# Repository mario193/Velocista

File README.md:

# Velocista
Un robot muy rápido

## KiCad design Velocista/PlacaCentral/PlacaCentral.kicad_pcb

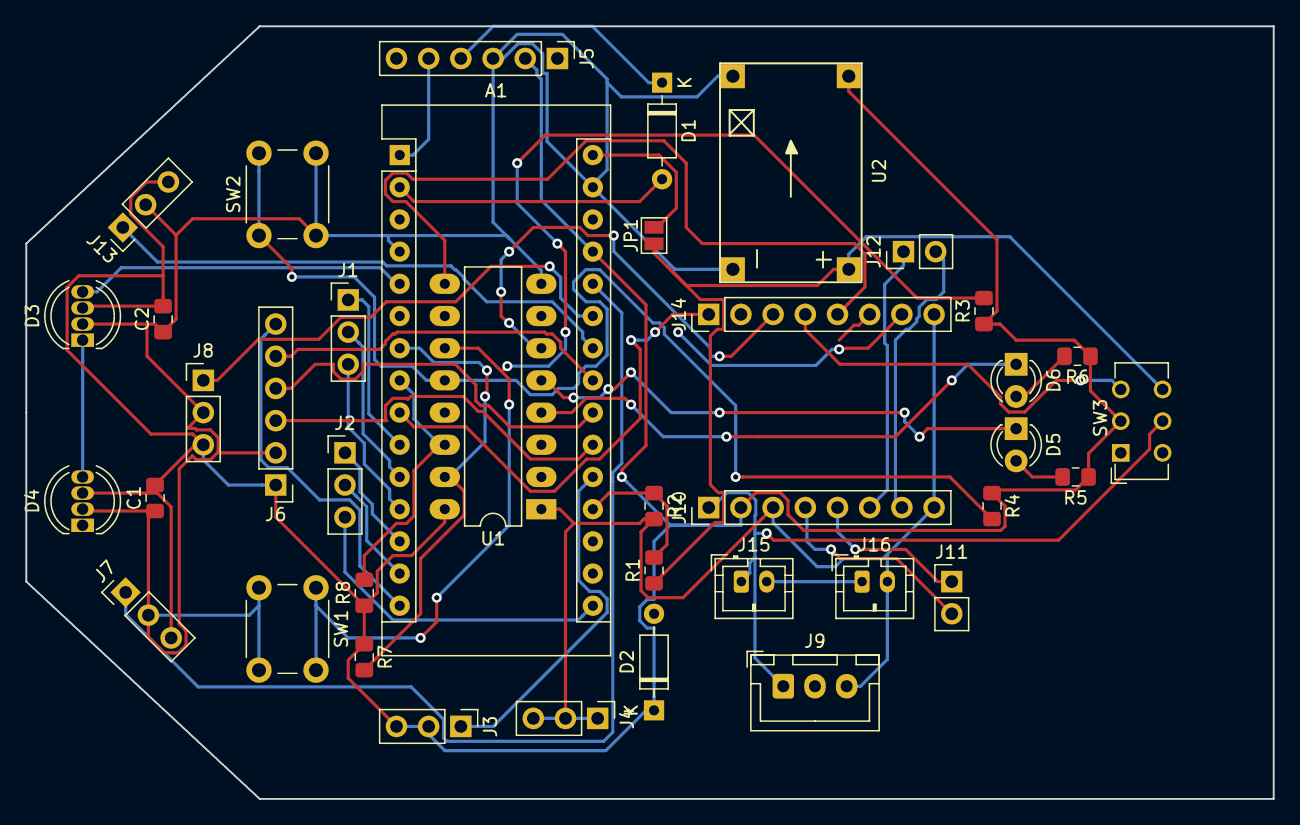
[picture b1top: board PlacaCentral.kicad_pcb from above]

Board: 2 copper layers, 98.4 x 61.0 mm, 39 parts (0 on the bottom side), 45 nets.

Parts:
A1: Arduino_Nano_v3.x; Arduino_Nano
C1, C2: 100nF; C_0805_2012Metric_Pad1.15x1.40mm_HandSolder
D1, D2: 1N4148; D_DO-35_SOD27_P7.62mm_Horizontal
D3: NEO1; LED_D5.0mm-4_RGB
D4: NEO2; LED_D5.0mm-4_RGB
D5: ROJO; LED_D3.0mm
D6: VERDE; LED_D3.0mm
J1: AUX1; PinHeader_1x03_P2.54mm_Vertical
J2: AUX2; PinHeader_1x03_P2.54mm_Vertical
J3: AUX3; PinHeader_1x03_P2.54mm_Vertical
J4: AUX4; PinHeader_1x03_P2.54mm_Vertical
J5: HC-05; PinHeader_1x06_P2.54mm_Vertical
J6: Sensores_linea; PinHeader_1x06_P2.54mm_Vertical
J7: DIST_IZQ; PinHeader_1x03_P2.54mm_Vertical
J8: DIST_FRONT; PinHeader_1x03_P2.54mm_Vertical
J9: LIPO_2S; JST_XH_B03B-XH-A_1x03_P2.50mm_Vertical
J10: TB6612FNG_A; PinHeader_1x08_P2.54mm_Vertical
J11: MOT_IZQ; PinHeader_1x02_P2.54mm_Vertical
J12: MOT_DER; PinHeader_1x02_P2.54mm_Vertical
J13: DIST_DCHA; PinHeader_1x03_P2.54mm_Vertical
J14: TB6612FNG_B; PinHeader_1x08_P2.54mm_Vertical
J15: LIPO_1S_A; JST_PH_B2B-PH-K_1x02_P2.00mm_Vertical
J16: LIPO_1S_B; JST_PH_B2B-PH-K_1x02_P2.00mm_Vertical
JP1: Jumper_NO_Small; SolderJumper-2_P1.3mm_Open_Pad1.0x1.5mm
R1: 82K; R_0805_2012Metric_Pad1.15x1.40mm_HandSolder
R2: 120K; R_0805_2012Metric_Pad1.15x1.40mm_HandSolder
R3, R4: 10K; R_0805_2012Metric_Pad1.15x1.40mm_HandSolder
R5, R6: 220; R_0805_2012Metric_Pad1.15x1.40mm_HandSolder
R7, R8: 1K; R_0805_2012Metric_Pad1.15x1.40mm_HandSolder
SW1: B1; SW_PUSH_6mm
SW2: B2; SW_PUSH_6mm
SW3: SW_DPDT_x2; SW_CuK_JS202011CQN_DPDT_Straight
U1: PCF8574; DIP-16_W7.62mm_LongPads
U2: DC-DC_BuckModule; DC-DC-MP2307

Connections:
12C_SCL: A1.8, R8.2, U1.14
12C_SDA: A1.7, R7.2, U1.15
+5V: A1.27, C1.2, C2.2, D2.1, D3.3, D4.3, J3.2, J3.3, J5.2, J6.1, J7.3, J8.3, J10.2, J13.3, R3.1, R4.1, R5.1, R6.1, R7.1, R8.1, SW3.2, U1.16, U2.3
A1: A1.20, J3.1
B1: R3.2, SW1.1, U1.11
B2: R4.2, SW2.1, U1.12
BAT: A1.19, D2.2, R1.2, R2.1
BT_RX: A1.1, J5.5
BT_TX: A1.2, D1.2
D7: A1.10, J1.1
D8: A1.11, J1.2
D9: A1.12, J1.3
D10: A1.13, J2.1
D11: A1.14, J2.2
D13: A1.16, J2.3
DIR_DER_1: J14.5, U1.9
DIR_DER_2: J14.6, U1.10
DIR_IZQ_1: J14.3, U1.6
DIR_IZQ_2: J14.2, U1.7
DIST_DCHA: A1.24, J13.1
DIST_FRONT: A1.25, J8.1
DIST_IZQ: A1.26, J7.1
GND: A1.4, A1.29, C1.1, C2.1, D3.2, D4.2, J4.1, J4.2, J4.3, J5.3, J6.2, J7.2, J8.2, J9.3, J10.3, J10.8, J13.2, J14.8, J16.2, R2.2, SW1.2, SW2.2, U1.1, U1.2, U1.3, U1.8, U2.2, U2.4
LED_G: D6.1, U1.4
LED_R: D5.1, U1.5
LINEA_1: A1.21, J6.3
LINEA_2: A1.22, J6.4
LINEA_3: A1.23, J6.5
LINEA_SEL: A1.15, J6.6
M_DER_+: J10.7, J12.2
M_DER_-: J10.6, J12.1
M_IZQ_+: J10.4, J11.2
M_IZQ_-: J10.5, J11.1
NEO: A1.5, D3.4
unnamed: D1.1, J5.4
unnamed: D3.1, D4.4
unnamed: D5.2, R5.2
unnamed: D6.2, R6.2
unnamed: J15.2, J16.1
PWM_DER: A1.6, J14.7
PWM_IZQ: A1.9, J14.1
STBY_MOT: J14.4, SW3.3
VBAT: J9.1, J10.1, J15.1, SW3.5
VCC: A1.30, JP1.2
VDD: JP1.1, R1.1, SW3.6, U2.1

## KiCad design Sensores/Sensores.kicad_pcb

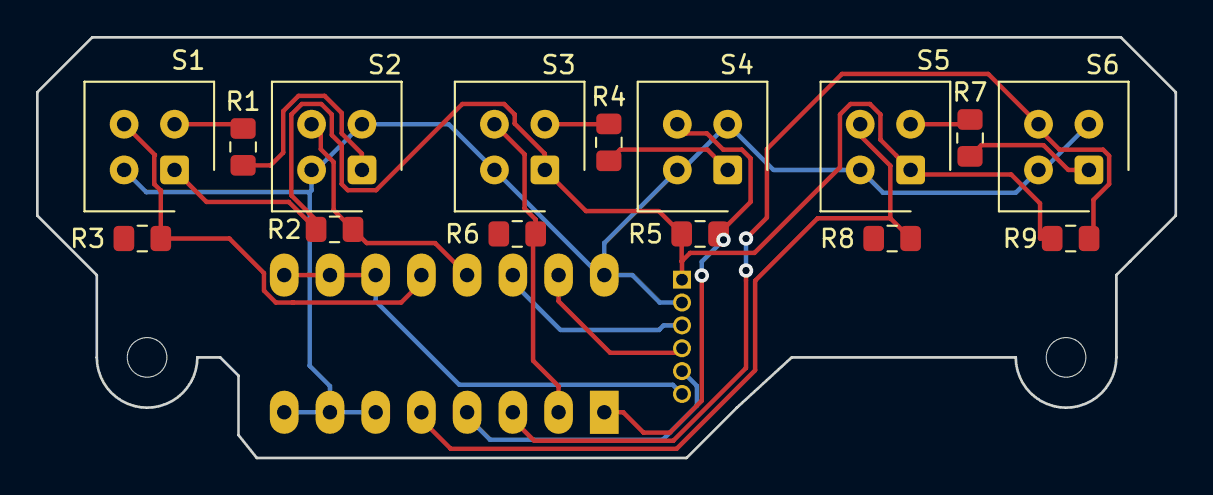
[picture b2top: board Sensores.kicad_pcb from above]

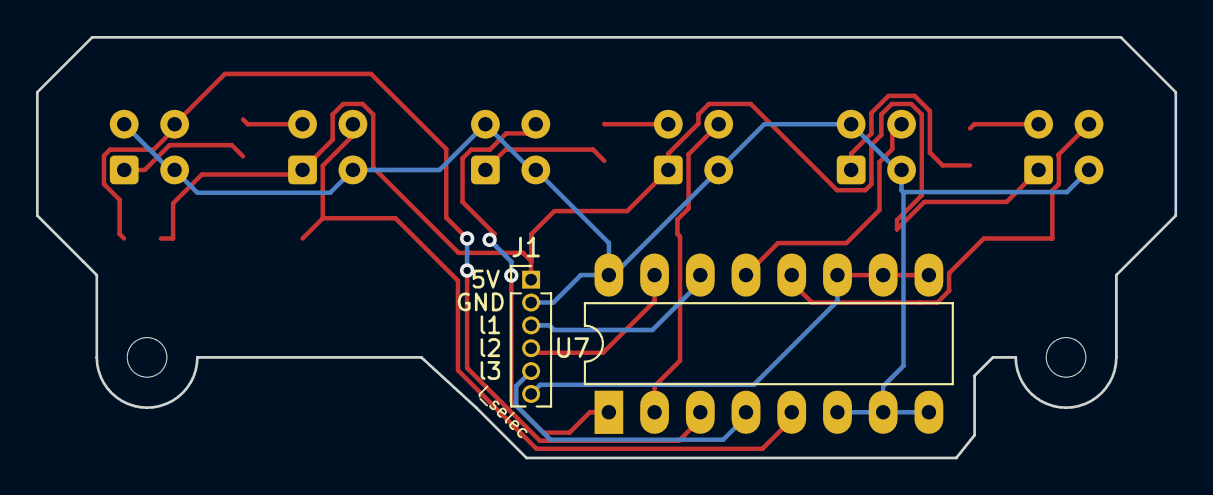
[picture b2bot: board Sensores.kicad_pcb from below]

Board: 2 copper layers, 63.2 x 23.4 mm, 17 parts (2 on the bottom side), 18 nets.

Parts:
J1: Conn_01x06_Female; PinHeader_1x06_P1.27mm_Vertical
R1, R4, R7: 82; R_0805_2012Metric_Pad1.15x1.40mm_HandSolder
R2, R3, R5, R6, R8, R9: 10k; R_0805_2012Metric_Pad1.15x1.40mm_HandSolder
S1, S2, S3, S4, S5, S6: CNY70; Vishay_CNY70
U7: 4053; DIP-16_W7.62mm_LongPads

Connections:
+5V: J1.1, R2.1, R5.1, R9.1, S1.1, S3.1, S5.1
/linea1: J1.3, U7.14
/linea2: J1.4, U7.15
/linea3: J1.5, U7.4
/linea_selec: J1.6, U7.9, U7.10, U7.11
/sensor1: R3.2, S1.3, U7.12
/sensor2: R2.2, S2.3, U7.13
/sensor3: R6.2, S3.3, U7.2
/sensor4: R5.2, S4.3, U7.1
/sensor5: R8.2, S5.3, U7.5
/sensor6: R9.2, S6.3, U7.3
GND: J1.2, S1.4, S2.2, S2.4, S3.4, S4.2, S4.4, S5.4, S6.2, S6.4, U7.6, U7.7, U7.8, U7.16
unnamed: R1.1, S1.2
unnamed: R1.2, S2.1
unnamed: R4.1, S3.2
unnamed: R4.2, S4.1
unnamed: R7.1, S5.2
unnamed: R7.2, S6.1

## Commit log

2018-12-15 Placa de los sensores y placa principal del robot
2018-12-15 Empezado el diseño de la placa principal
2018-12-22 Terminada distribución de componentes y enrutado
2019-01-12 Terminado de enrutar.
2019-01-12 Terminado de enrutar
